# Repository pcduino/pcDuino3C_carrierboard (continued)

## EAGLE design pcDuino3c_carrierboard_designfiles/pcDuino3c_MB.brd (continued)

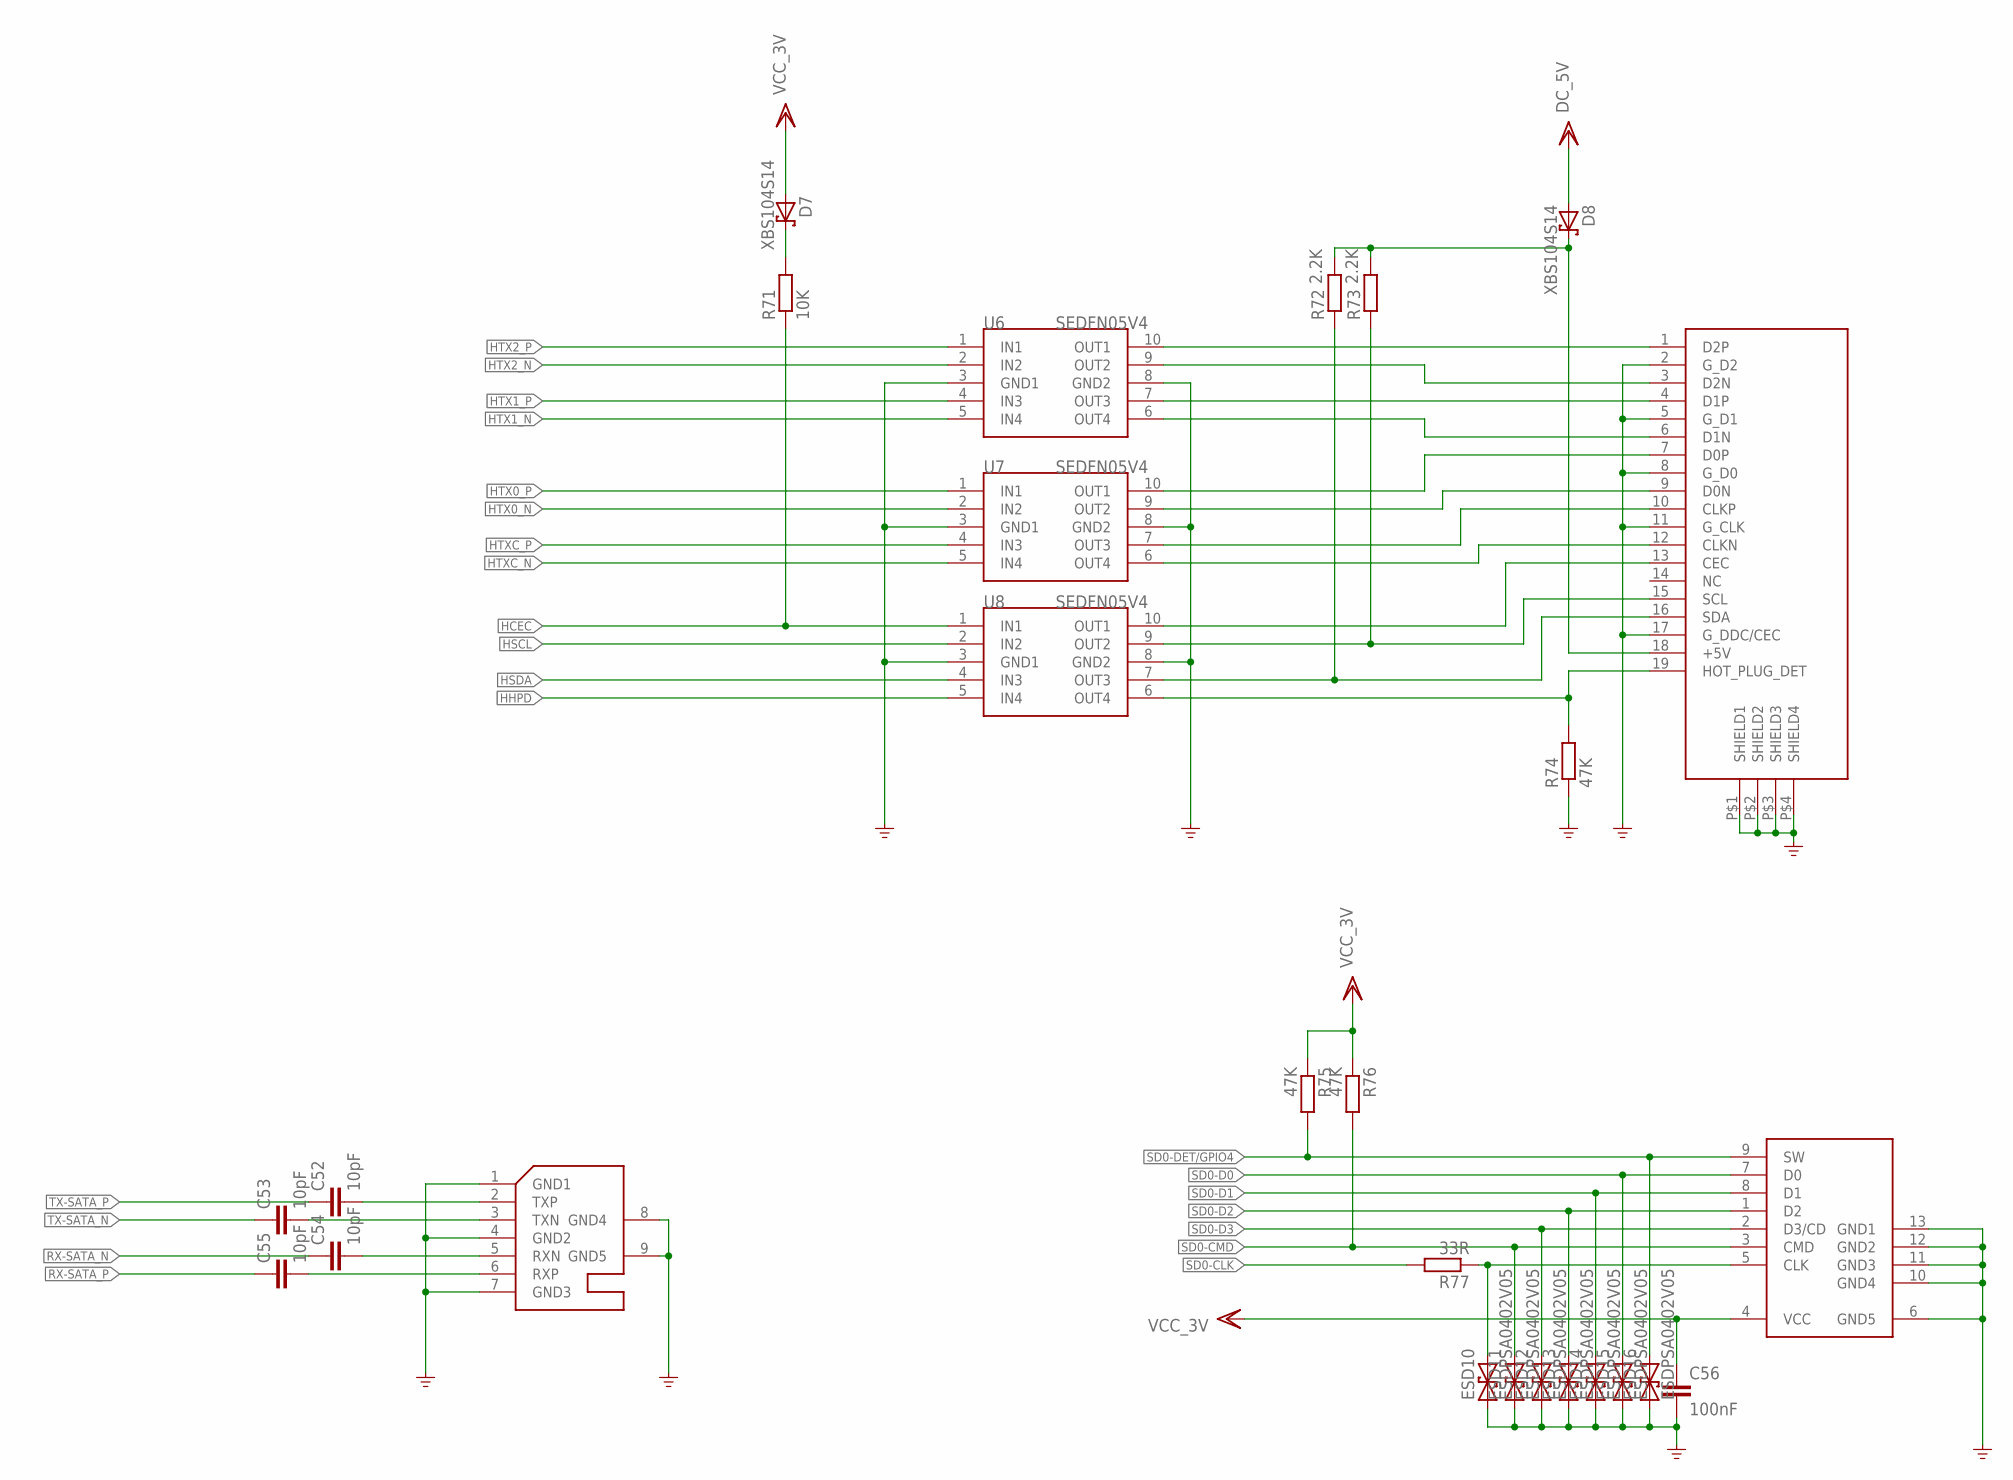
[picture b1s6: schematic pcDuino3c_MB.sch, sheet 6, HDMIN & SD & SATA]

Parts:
C52, C53, C54, C55: 10pF; C0402K
C56: 100nF; C0402K
D7, D8: XBS104S14; D1206
ESD10, ESD11, ESD12, ESD13, ESD14, ESD15, ESD16: ESDPSA0402V05; R0402
J11: CON-HDMI
J12: SOCKET-MICROSD
J13: CON-SATA
R71: 10K; R0402
R72, R73: 2.2K; R0402
R74, R75, R76: 47K; R0402
R77: 33R; R0402
U6, U7, U8: SEDFN05V4; RCLAMP0524P_1PRIMARY

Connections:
DC_5V: D8.+ (A); also elsewhere on the board
GND: C56.1, ESD10.1, ESD11.1, ESD12.1, ESD13.1, ESD14.1, ESD15.1, ESD16.1, J11.2 (G_D2), J11.5 (G_D1), J11.8 (G_D0), J11.11 (G_CLK), J11.17 (G_DDC/CEC), J11.P$1 (SHIELD1), J11.P$2 (SHIELD2), J11.P$3 (SHIELD3), J11.P$4 (SHIELD4), J12.6 (GND5), J12.10 (GND4), J12.11 (GND3), J12.12 (GND2), J12.13 (GND1), J13.1 (GND1), J13.4 (GND2), J13.7 (GND3), J13.8 (GND4), J13.9 (GND5), R74.1, U6.3 (GND1), U6.8 (GND2), U7.3 (GND1), U7.8 (GND2), U8.3 (GND1), U8.8 (GND2); also elsewhere on the board
HCEC: J11.13 (CEC), R71.1, U8.1 (IN1), U8.10 (OUT1); also elsewhere on the board
HHPD: J11.19 (HOT_PLUG_DET), R74.2, U8.5 (IN4), U8.6 (OUT4); also elsewhere on the board
HSCL: J11.15 (SCL), R73.1, U8.2 (IN2), U8.9 (OUT2); also elsewhere on the board
HSDA: J11.16 (SDA), R72.1, U8.4 (IN3), U8.7 (OUT3); also elsewhere on the board
HTX0_N: J11.9 (D0N), U7.2 (IN2), U7.9 (OUT2); also elsewhere on the board
HTX0_P: J11.7 (D0P), U7.1 (IN1), U7.10 (OUT1); also elsewhere on the board
HTX1_N: J11.6 (D1N), U6.5 (IN4), U6.6 (OUT4); also elsewhere on the board
HTX1_P: J11.4 (D1P), U6.4 (IN3), U6.7 (OUT3); also elsewhere on the board
HTX2_N: J11.3 (D2N), U6.2 (IN2), U6.9 (OUT2); also elsewhere on the board
HTX2_P: J11.1 (D2P), U6.1 (IN1), U6.10 (OUT1); also elsewhere on the board
HTXC_N: J11.12 (CLKN), U7.5 (IN4), U7.6 (OUT4); also elsewhere on the board
HTXC_P: J11.10 (CLKP), U7.4 (IN3), U7.7 (OUT3); also elsewhere on the board
unnamed: D8.- (C), J11.18 (+5V), R72.2, R73.2
unnamed: D7.- (C), R71.2
unnamed: C52.2, J13.2 (TXP)
unnamed: C53.2, J13.3 (TXN)
unnamed: C54.2, J13.5 (RXN)
unnamed: C55.2, J13.6 (RXP)
unnamed: ESD10.2, J12.5 (CLK), R77.1
RX-SATA_N: C54.1; also elsewhere on the board
RX-SATA_P: C55.1; also elsewhere on the board
SD0-CLK: R77.2; also elsewhere on the board
SD0-CMD: ESD11.2, J12.3 (CMD), R76.2; also elsewhere on the board
SD0-D0: ESD15.2, J12.7 (D0); also elsewhere on the board
SD0-D1: ESD14.2, J12.8 (D1); also elsewhere on the board
SD0-D2: ESD13.2, J12.1 (D2); also elsewhere on the board
SD0-D3: ESD12.2, J12.2 (D3/CD); also elsewhere on the board
SD0-DET/GPIO4: ESD16.2, J12.9 (SW), R75.2; also elsewhere on the board
TX-SATA_N: C53.1; also elsewhere on the board
TX-SATA_P: C52.1; also elsewhere on the board
VCC_3V: C56.2, D7.+ (A), J12.4 (VCC), R75.1, R76.1; also elsewhere on the board

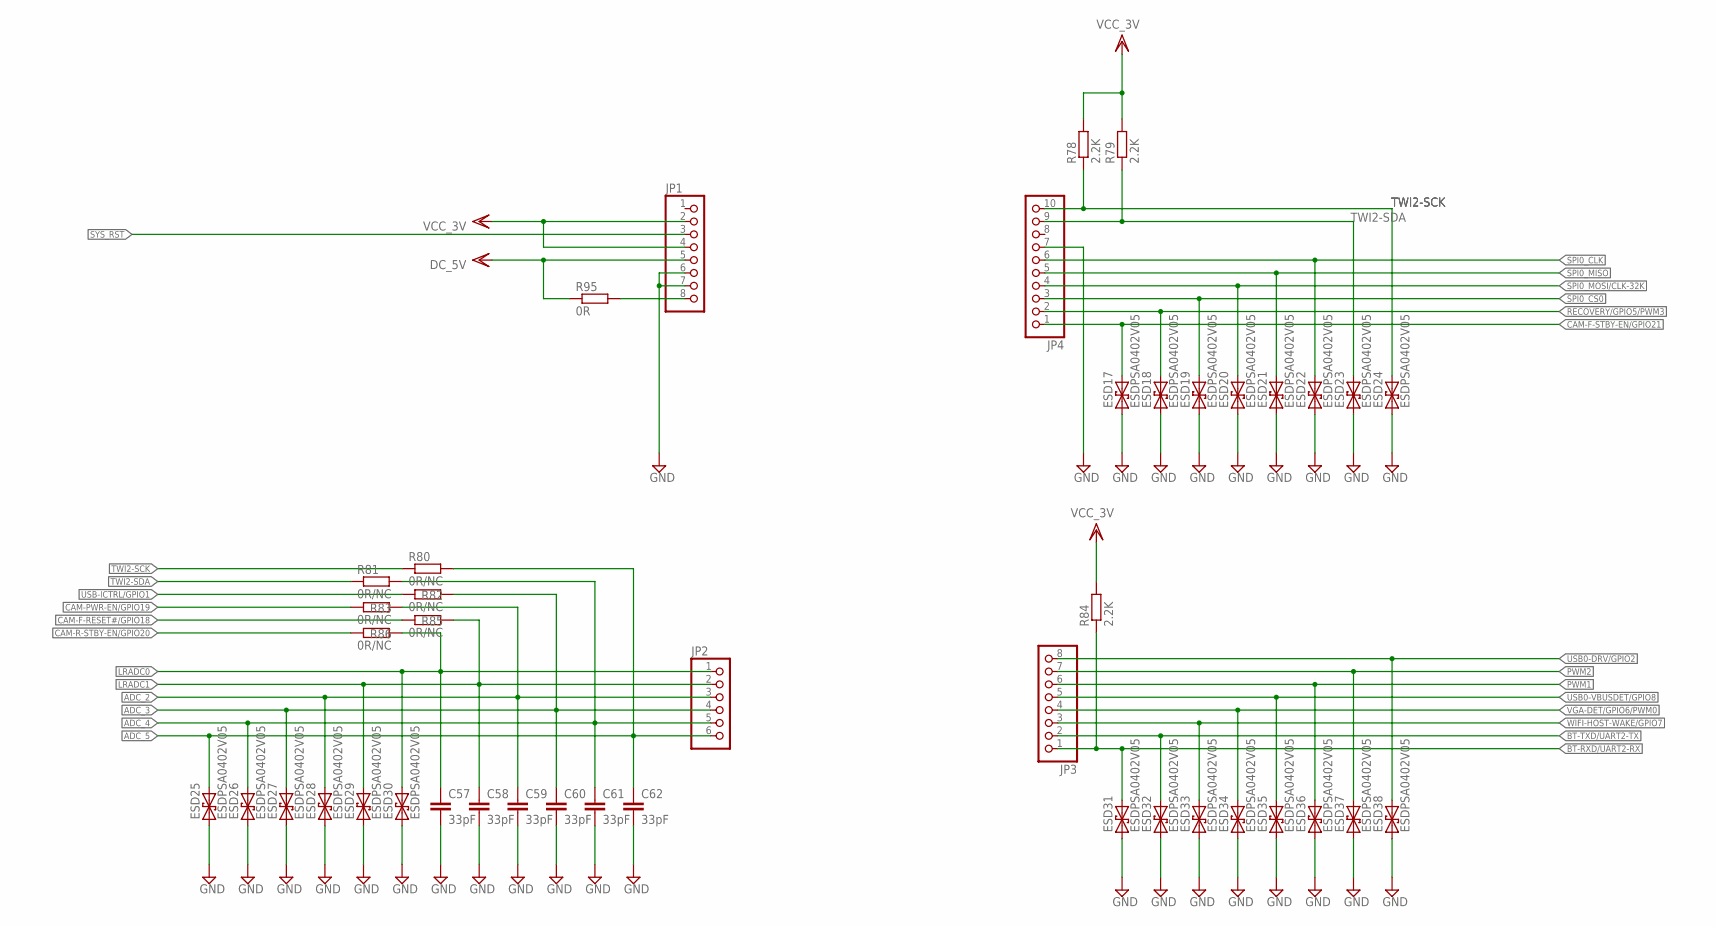
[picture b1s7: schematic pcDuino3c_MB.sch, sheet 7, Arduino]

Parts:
C57, C58, C59, C60, C61, C62: 33pF; C0402K
ESD17, ESD18, ESD19, ESD20, ESD21, ESD22, ESD23, ESD24, ESD25, ESD26, ESD27, ESD28, ESD29, ESD30, ESD31, ESD32, ESD33, ESD34, ESD35, ESD36, ESD37, ESD38: ESDPSA0402V05; R0402
JP1, JP3: PINHD-1X8; 1X08
JP2: PINHD-1X6; 1X06
JP4: PINHD-1X10; 1X10
R78, R79, R84: 2.2K; R0402
R80, R81, R82, R83, R85, R86: 0R/NC; R0402
R95: 0R; R0805

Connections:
ADC_2: C59.1, ESD28.2, JP2.3, R83.2; also elsewhere on the board
ADC_3: C60.1, ESD27.2, JP2.4, R82.2; also elsewhere on the board
ADC_4: C61.1, ESD26.2, JP2.5, R81.2; also elsewhere on the board
ADC_5: C62.1, ESD25.2, JP2.6, R80.2; also elsewhere on the board
BT-RXD/UART2-RX: ESD31.2, JP3.1, R84.1; also elsewhere on the board
BT-TXD/UART2-TX: ESD32.2, JP3.2; also elsewhere on the board
CAM-F-RESET#/GPIO18: R85.1; also elsewhere on the board
CAM-F-STBY-EN/GPIO21: ESD17.2, JP4.1; also elsewhere on the board
CAM-PWR-EN/GPIO19: R83.1; also elsewhere on the board
CAM-R-STBY-EN/GPIO20: R86.1; also elsewhere on the board
DC_5V: JP1.5, R95.1; also elsewhere on the board
GND: C57.2, C58.2, C59.2, C60.2, C61.2, C62.2, ESD17.1, ESD18.1, ESD19.1, ESD20.1, ESD21.1, ESD22.1, ESD23.1, ESD24.1, ESD25.1, ESD26.1, ESD27.1, ESD28.1, ESD29.1, ESD30.1, ESD31.1, ESD32.1, ESD33.1, ESD34.1, ESD35.1, ESD36.1, ESD37.1, ESD38.1, JP1.6, JP1.7, JP4.7; also elsewhere on the board
LRADC0: C57.1, ESD30.2, JP2.1, R86.2; also elsewhere on the board
LRADC1: C58.1, ESD29.2, JP2.2, R85.2; also elsewhere on the board
unnamed: JP1.8, R95.2
PWM1: ESD36.2, JP3.6; also elsewhere on the board
PWM2: ESD37.2, JP3.7; also elsewhere on the board
RECOVERY/GPIO5/PWM3: ESD18.2, JP4.2; also elsewhere on the board
SPI0_CLK: ESD22.2, JP4.6; also elsewhere on the board
SPI0_CS0: ESD19.2, JP4.3; also elsewhere on the board
SPI0_MISO: ESD21.2, JP4.5; also elsewhere on the board
SPI0_MOSI/CLK-32K: ESD20.2, JP4.4; also elsewhere on the board
SYS_RST: JP1.3; also elsewhere on the board
TWI2-SCK: ESD24.2, JP4.10, R78.1, R80.1; also elsewhere on the board
TWI2-SDA: ESD23.2, JP4.9, R79.1, R81.1; also elsewhere on the board
USB0-DRV/GPIO2: ESD38.2, JP3.8; also elsewhere on the board
USB0-VBUSDET/GPIO8: ESD35.2, JP3.5; also elsewhere on the board
USB-ICTRL/GPIO1: R82.1; also elsewhere on the board
VCC_3V: JP1.2, JP1.4, R78.2, R79.2, R84.2; also elsewhere on the board
VGA-DET/GPIO6/PWM0: ESD34.2, JP3.4; also elsewhere on the board
WIFI-HOST-WAKE/GPIO7: ESD33.2, JP3.3; also elsewhere on the board

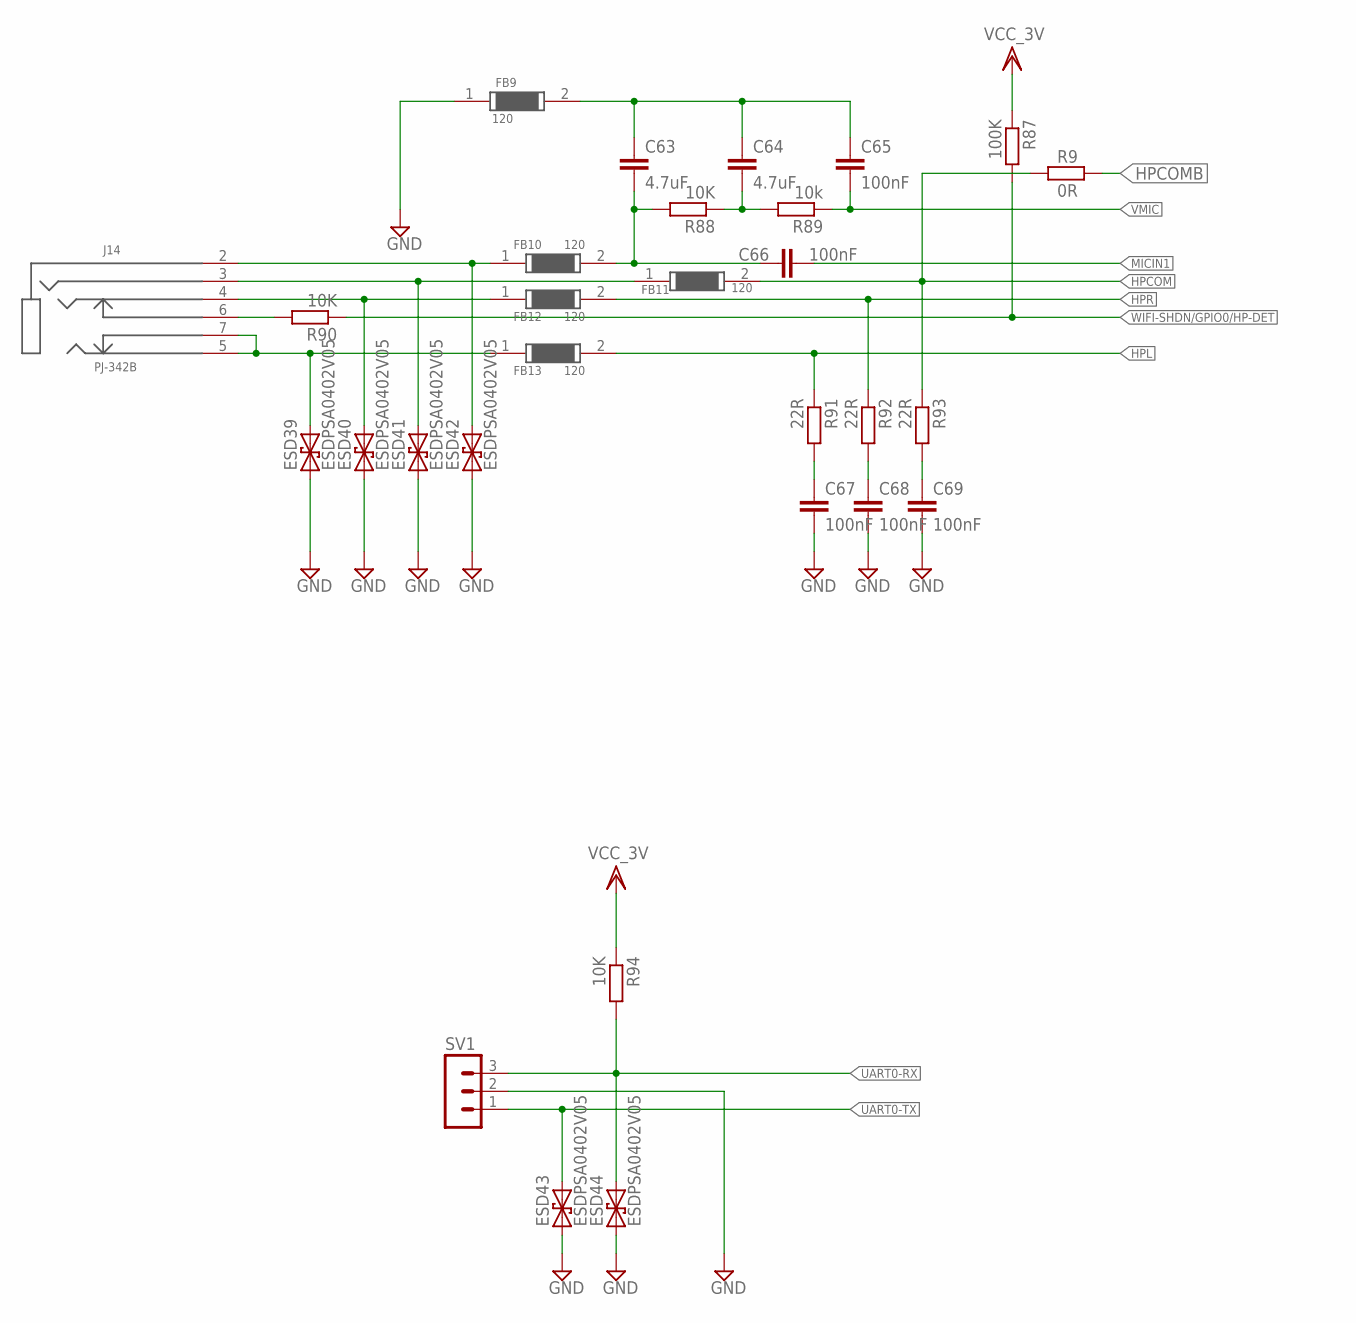
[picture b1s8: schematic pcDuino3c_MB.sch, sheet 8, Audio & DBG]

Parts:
C63, C64: 4.7uF; C0402K
C65, C66, C67, C68, C69: 100nF; C0402K
ESD39, ESD40, ESD41, ESD42, ESD43, ESD44: ESDPSA0402V05; R0402
FB9, FB10, FB11, FB12, FB13: 120; R0603
J14: PJ-342B
R9: 0R; R0402
R87: 100K; R0402
R88, R90, R94: 10K; R0402
R89: 10k; R0402
R91, R92, R93: 22R; R0402
SV1: MA03-1

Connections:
GND: C67.2, C68.2, C69.2, ESD39.1, ESD40.1, ESD41.1, ESD42.1, ESD43.1, ESD44.1, FB9.1, SV1.2; also elsewhere on the board
HPCOM: FB11.2, R9.1, R93.1; also elsewhere on the board
HPCOMB: R9.2; also elsewhere on the board
HPL: FB13.2, R91.1; also elsewhere on the board
HPR: FB12.2, R92.1; also elsewhere on the board
MICIN1: C66.2; also elsewhere on the board
unnamed: ESD41.2, FB11.1, J14.3
unnamed: ESD40.2, FB12.1, J14.4
unnamed: ESD42.2, FB10.1, J14.2
unnamed: ESD39.2, FB13.1, J14.5, J14.7
unnamed: C67.1, R91.2
unnamed: C68.1, R92.2
unnamed: C69.1, R93.2
unnamed: C63.2, C66.1, FB10.2, R88.2
unnamed: C64.2, R88.1, R89.2
unnamed: C63.1, C64.1, C65.1, FB9.2
unnamed: J14.6, R90.2
UART0-RX: ESD44.2, R94.2, SV1.3; also elsewhere on the board
UART0-TX: ESD43.2, SV1.1; also elsewhere on the board
VCC_3V: R87.1, R94.1; also elsewhere on the board
VMIC: C65.2, R89.1; also elsewhere on the board
WIFI-SHDN/GPIO0/HP-DET: R87.2, R90.1; also elsewhere on the board

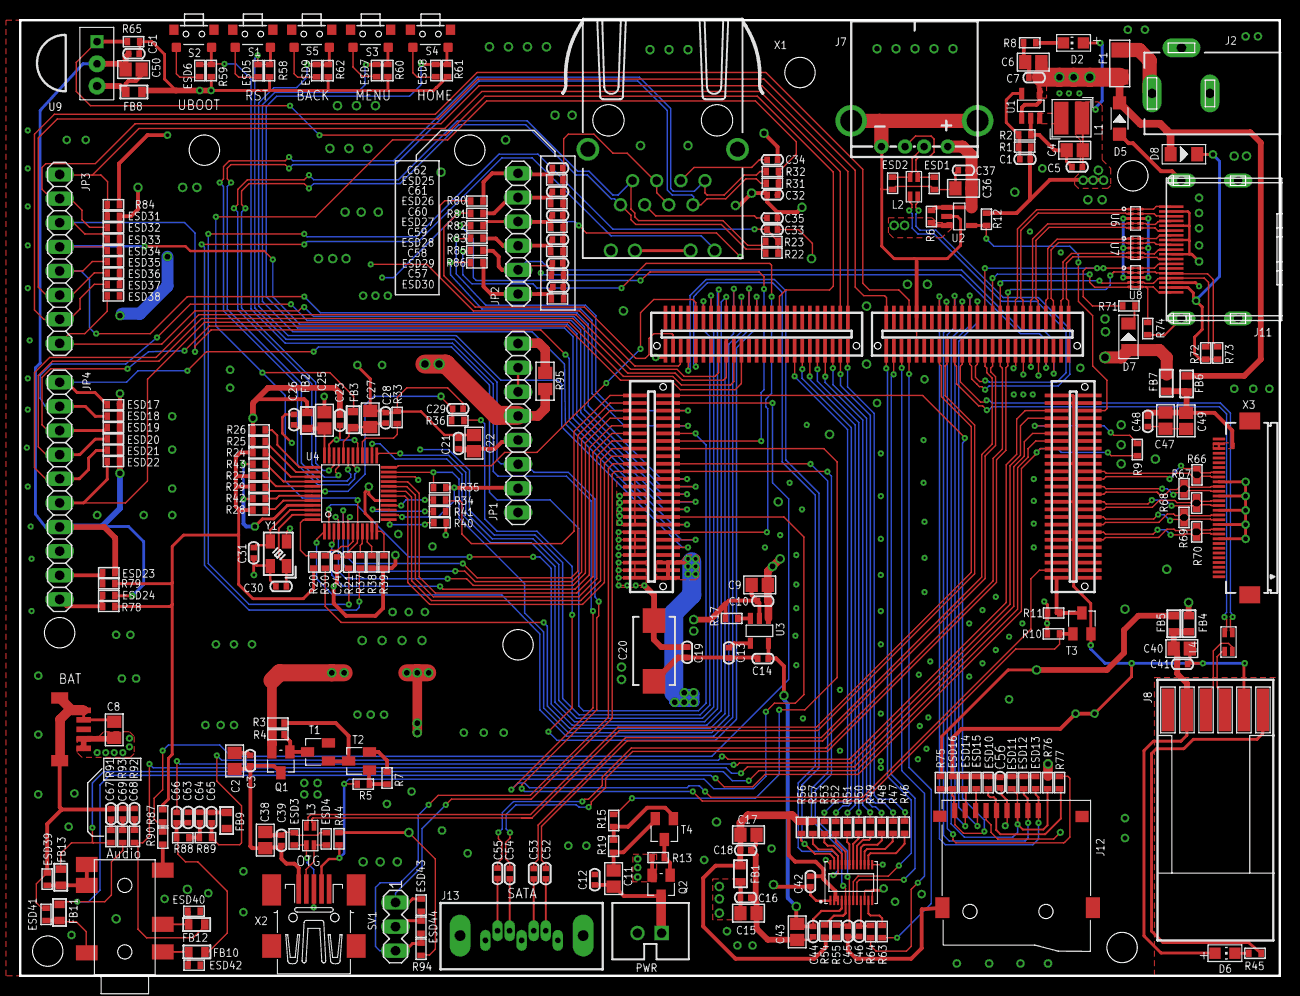
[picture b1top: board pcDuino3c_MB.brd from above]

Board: 4 copper layers, 132.6 x 100.6 mm, 270 parts (0 on the bottom side), 209 nets.

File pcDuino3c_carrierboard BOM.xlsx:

| Qty | Value | Device | Package | Parts
 | Connectors
 | 1 | BTB-50PIN-0.8 | 50P socket | SMT | J3 J4 J5 J15
 | 1 | 1x3P 2.54mm | single row header | plug | SV1
 | 1 | 1X10P 2.54mm | single row socket | plug | JP4
 | 1 | 1X6P 2.54mm | single row socket | plug | JP2
 | 2 | 1X8P 2.54mm | single row socket | plug | JP1,JP3
 | 1 | CON-BAT | CON-BAT | CON-BAT-5P-1MM | J1
 | 1 | CON-HDMI | CON-HDMI | HDMI 19plug type A | J11
 | 1 | CON-SATA | CON-SATA | CON-SATA | J13
 | 1 | CON-USB | CON-USB | CON-USB | J7
 | 1 | DCJ0202 | DCJ0202 | DCJ0202 | J2
 | 1 | J1011F01P | network transformer | plug | X1 |  |  |  |  |  |  | unknown
 | 1 | MINI-USB | USB socket | SMT | X2
 | 5 | SMD_KEY | SMD_KEY | SMT | S1,S2,S3,S4,S5
 | 1 | XH-2 2.54mm | XH-2 socket | plug | PWR
 | 1 | FPC-30P-0.5 | FPC connector | FH12-30S-0.5SH | X3 |  |  |  |  |  |  | 1324555 | 34M6176
 | 1 | SOCKET-MICROSD | SOCKET-MICROSD | SOCKET-MICROSD | J12
 | Resistors
 | 2 | 0R | R-EU_R0402 | R0402 | R9,R21
 | 1 | 0R | R-EU_R0805 | R0805 | R95
 | 7 | 0R/NC | R-EU_R0402 | R0402 | R6,R80,R81,R82,R83,R85,R86,R36
 | 4 | 100K | R-EU_R0402 | R0402 | R5,R29,R55,R87
 | 1 | 100K/1% | R-EU_R0402 | R0402 | R1
 | 1 | 100R | R-EU_R0402 | R0402 | R30,R34
 | 5 | 100R/NC | R-EU_R0402 | R0402 | R66,R67,R68,R69,R70
 | 29 | 10K | R-EU_R0402 | R0402 | R10,R12,R15,R17,R20,R24,R25,R26,R27,R28,R35,R37,R38,R39,R40,R41,R42,R54,R56,R57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
 | 2 | 10k | R-EU_R0402 | R0402 | R43,R89
 | 1 | 1K | R-EU_R0402 | R0402 | R8
 | 5 | 2.2K | R-EU_R0402 | R0402 | R72,R73,R78,R79,R84
 | 1 | 22K/1% | R-EU_R0402 | R0402 | R2
 | 13 | 22R | R-EU_R0402 | R0402 | R46,R47,R48,R49,R50,R51,R52,R53,R63,R64,R91,R92,R93
 | 1 | 33R | R-EU_R0402 | R0402 | R77
 | 7 | 47K | R-EU_R0402 | R0402 | R3,R4,R7,R13,R19,R74,R75,R76
 | 4 | 49.9R/1% | R-EU_R0402 | R0402 | R22,R23,R31,R32
 | 2 | 510R | R-EU_R0402 | R0402 | R11,R45
 | 1 | 6.2K/1% | R-EU_R0402 | R0402 | R33
 | 2 | 4.7K | R-EU_R0402 | R0402 | R44,R65
 | Capacitor
 | 27 | 100nF | C-EUC0402K | C0402 | C3,C5,C7,C12,C16,C18,C19,C21,C23,C24,C26,C28,C32,C33,C34,C35,C37,C39,C42,C44,C5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
 | 4 | 100nF | C-EUC0805 | C0805 | C9,C40,C49,C50
 | 1 | 100pF | C-EUC0402K | C0402 | C48
 | 4 | 10pF | C-EUC0402K | C0402 | C52,C53,C54,C55
 | 1 | 10uF | C-EUC0402K | C0402 | C41
 | 9 | 10uF | C-EUC0805 | C0805 | C2,C4,C6,C8,C22,C25,C27,C36,C38
 | 2 | 18pF | C-EUC0402K | C0402 | C30,C31
 | 4 | 1uF | C-EUC0402K | C0402 | C10,C14,C29,C45
 | 3 | 1uF | C-EUC0805 | C0805 | C15,C17,C43
 | 1 | 22nF | C-EUC0402K | C0402 | C13
 | 1 | 22pF/NC | C-EUC0402K | C0402 | C46
 | 1 | 22uF | C-EUC0805 | C0805 | C47
 | 1 | 22uF/16V | C-EUC0805 | C0805 | C11
 | 6 | 33pF | C-EUC0402K | C0402 | C57,C58,C59,C60,C61,C62
 | 2 | 4.7uF | C-EUC0402K | C0402 | C63,C64
 | 1 | 4.7uF | CPOL-EUCT7343 | CT7343 | C20
 | 1 | 47pF | C-EUC0402K | C0402 | C1
 | Inductor, bead, crystal, fuse
 | 1 | 2A_SMD | PTCFUSE-1206 | R1206 | F1
 | 4 | 120R@300mA |  | R0603 | FB9,FB10,FB11,FB12,FB13
 | 5 | 47R@500mA |  | R0603 | FB2,FB3,FB4,FB5,FB6
 | 2 | LI0603EXXXR-10 | LI0603EXXXR-10 | R0603 | FB1,FB8
 | 1 | 4.7uH/1.5A | INDICATORCD32 | CD32 | L1
 | 3 | IND-CL-2M2012 | Inductor | CL-2M2012 | L2,L3,L4
 | 1 | 25MHz | passive crystal | 3225 | Y1
 | 1 | NC | LI0603EXXXR-10 | R0603 | FB7
 | Diode, transistor, MOS
 | 1 | LED | LED-BLUE | LED-0805 | D6
 | 1 | LED | LED-GREEN | LED-0805 | D2
 | 2 | AO3401 | P-MOS | SOT23 | Q1,Q2
 | 4 | MMBT3904 | NPN Transistor | SOT23 | T1,T2,T3,T4
 | 1 | MMSZ5232B | DIODE-SMD2010 | D2010 | D5
 | 2 | XBS104S14 | SCHOTTKY | D1206 | D7,D8
 | 44 | ESDPSA0402V05 | ESDPSA0402V05 | R0402 | ESD1,ESD2,ESD3,ESD4,ESD5,ESD6,ESD7,ESD8,ESD9,ESD10,ESD11,ESD12,ESD13,ESD14,ESD1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
 | IC
 | 1 | INFARED | INFARED | HS/VS1838 | U9
 | 1 | IP101ALF | IP101ALF | LQFP48 | U4
 | 1 | PJ-342B | PJ-342B | PJ-342B | J14
 | 1 | AXK824145WG | CAM Male | 12x2P 0.4mm | J10
 | 1 | RT9193GB | RT9193GB | SOT23-5 | U3
 | 1 | RT9701GB | RT9701GB | SOT23-5 | U2
 | 1 | RTL8188CUS | WIFI Mould | PCDUINO-WIFI-0_1PRIMARY | J8
 | 3 | RCLAMP0524P | SEDFN05V4 | RCLAMP0524P | U6,U7,U8
 | 1 | SY8088 | SY8088 | SOT23-5 | U1

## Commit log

2015-03-08 pcDuino3c carrier board first release
    pcDuino3c carrier board first release
